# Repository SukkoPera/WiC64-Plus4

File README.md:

# WiC64-Plus4

WiC64-Plus4 is a WiFi network interface compatible with the Commodore 64, Commodore 16, 116 and Plus/4 computers.

## Summary
This is a slightly modified version of the [WiC64](https://github.com/WiC64-Team/wic64-hardware) board by GMP.

The most significant change is that the board can now be powered with either +5VDC or 9VAC.

This was done in order to make it easier to use the board on the Commodore 16 and Plus/4, where it must be connected through [an intermediate board](https://github.com/SukkoPera/PlusVIA) which only provides +5VDC.

Selection of the power source is automatic. If both power sources are available the higher one will take precedence. This means that **the board retains full compatibility with the C64**, and it will still use the 9VAC supply when connected to it.

Since the board might have a quite impulsive power draw, a ferrite bead was added on the +5VDC rail in order to reduce any interference.

Finally, to make hand-assembly easier, the 0603 components were switch to 0805 and the pads for the SOT-23 MOSFETs where made longer.

## Usage and Programming
This version of the board is **100% compatible with the original** one.

Please refer to [the original project](https://github.com/WiC64-Team/wic64-hardware) for assembly instructions, BOM (note you will need an extra 1n5819 diode) and 3D-printable enclosures.

The board is supposed to be used with [the original firmware](https://github.com/WiC64-Team/wic64-firmware).

For software support, I have made [a modified version of the interface library](https://github.com/SukkoPera/wic64-library) that allows writing software for either the C64 or C16/Plus4, but the board also works with the original library when used on the C64.

## Releases
If you want to get this board produced, you are recommended to get [the latest release](https://github.com/SukkoPera/WiC64-Plus4/releases) rather than the current git version, as the latter might be under development and is not guaranteed to be working.

Every release is accompanied by its Bill Of Materials (BOM) file and any relevant notes about it, which you are recommended to read carefully.

## License
The WiC64-Plus4 documentation, including the design itself, is copyright &copy; 2021 GMP and SukkoPera 2024-2026 and is licensed under the [Creative Commons Attribution 4.0 International License](https://creativecommons.org/licenses/by/4.0/).

This documentation is distributed *as is* and WITHOUT ANY EXPRESS OR IMPLIED WARRANTIES whatsoever with respect to its functionality, operability or use, including, without limitation, any implied warranties OF MERCHANTABILITY, SATISFACTORY QUALITY, FITNESS FOR A PARTICULAR PURPOSE or infringement. We expressly disclaim any liability whatsoever for any direct, indirect, consequential, incidental or special damages, including, without limitation, lost revenues, lost profits, losses resulting from business interruption or loss of data, regardless of the form of action or legal theory under which the liability may be asserted, even if advised of the possibility or likelihood of such damages.

## Support the Project
If you want to get some boards manufactured, you can get them from PCBWay through this link:

You get my gratitude and cheap, professionally-made and good quality PCBs, I get some credit that will help with this and [other projects](https://www.pcbway.com/project/member/shareproject/?bmbid=41100). You won't even have to worry about the various PCB options, it's all pre-configured for you!

Also, if you still have to register, [you can use this link](https://www.pcbway.com/setinvite.aspx?inviteid=41100) to get some bonus initial credit (and earn me some more).

You can also buy me a coffee if you want.

## Thanks
* GMP and the WiC64 team for the original board, library and whole concept.

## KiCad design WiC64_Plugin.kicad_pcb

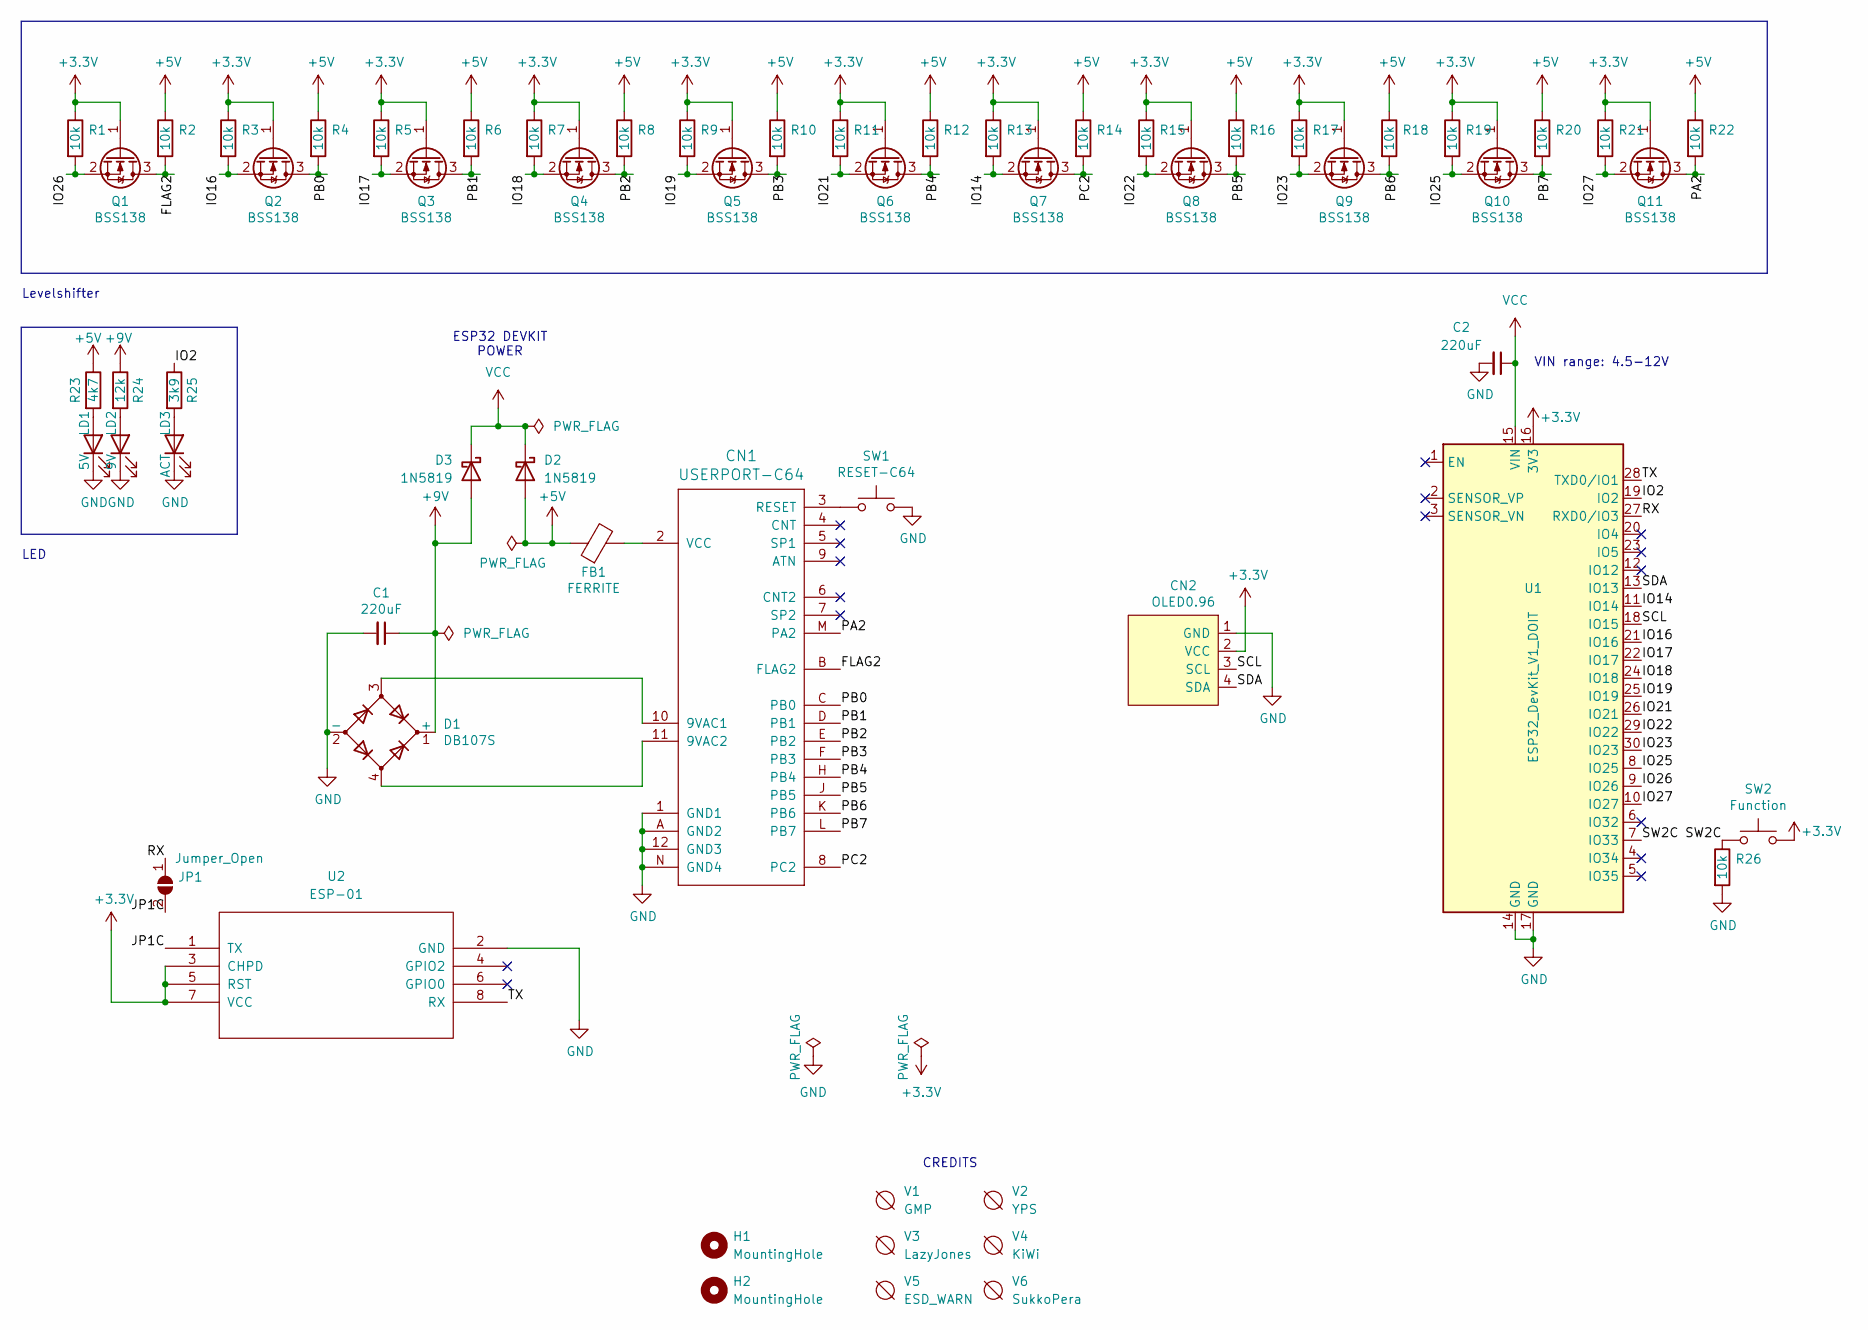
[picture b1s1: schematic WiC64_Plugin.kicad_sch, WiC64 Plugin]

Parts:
C1: 220uF; CP_6.3x11mm_horiz-R; LCSC C269997
C2: 220uF; CP_6.3x11mm_horiz-R; LCSC C106598
CN1: USERPORT-C64; UPS24CONN
CN2: OLED0.96; PinSocket_1x04_P2.54mm_Vertical
D1: DB107S; Diode_Bridge_Diotec_SO-DIL-Slim; LCSC C190797
D2, D3: 1N5819; D_SMA; LCSC C402219
FB1: FERRITE; Ferrite_D6.0mm_L10.00mm_Horizontal
H1, H2: MountingHole; MountingHole_3.2mm_M3_ISO7380
JP1: Jumper_Open; SolderJumper-2_P1.3mm_Open_RoundedPad1.0x1.5mm
LD1: 5V; LED_D3.0mm; LCSC C568936
LD2: 9V; LED_D3.0mm; LCSC C568937
LD3: ACT; LED_D3.0mm; LCSC C331056
Q1, Q2, Q3, Q4, Q5, Q6, Q7, Q8, Q9, Q10, Q11: BSS138; SOT-23; LCSC C112239
R1, R2, R3, R4, R5, R6, R7, R8, R9, R10, R11, R12, R13, R14, R15, R16, R17, R18, R19, R20, R21, R22, R26: 10k; R_0805_2012Metric_Pad1.20x1.40mm_HandSolder; LCSC C25804
R23: 4k7; R_0805_2012Metric_Pad1.20x1.40mm_HandSolder; LCSC C23162
R24: 12k; R_0805_2012Metric_Pad1.20x1.40mm_HandSolder; LCSC C22790
R25: 3k9; R_0805_2012Metric_Pad1.20x1.40mm_HandSolder; LCSC C23018
SW1: RESET-C64; SW_Tactile_SPST_Angled_PTS645Vx58-2LFS; LCSC C406160
SW2: Function; SW_Tactile_SPST_Angled_PTS645Vx58-2LFS; LCSC C406160
U1: ESP32_DevKit_V1_DOIT; esp32_devkit_v1_doit
U2: ESP-01
V1: GMP
V2: YPS; YPS2
V3: LazyJones; LazyJones2
V4: KiWi
V5: ESD_WARN; ESD-Logo_6.6x6mm_SilkScreen
V6: SukkoPera; PearLogo

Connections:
+3.3V: CN2.2 (VCC), Q1.1 (G), Q2.1 (G), Q3.1 (G), Q4.1 (G), Q5.1 (G), Q6.1 (G), Q7.1 (G), Q8.1 (G), Q9.1 (G), Q10.1 (G), Q11.1 (G), R1.1, R3.1, R5.1, R7.1, R9.1, R11.1, R13.1, R15.1, R17.1, R19.1, R21.1, SW2.2, U1.16 (3V3), U2.3 (CHPD), U2.5 (RST), U2.7 (VCC)
+5V: D2.2 (A), FB1.1, R2.1, R4.1, R6.1, R8.1, R10.1, R12.1, R14.1, R16.1, R18.1, R20.1, R22.1, R23.1
+9V: C1.1, D1.1 (+), D3.2 (A), R24.1
/FLAG2: CN1.B (FLAG2), Q1.3 (D), R2.2
/IO2: R25.1, U1.19 (IO2)
/IO14: Q7.2 (S), R13.2, U1.11 (IO14)
/IO16: Q2.2 (S), R3.2, U1.21 (IO16)
/IO17: Q3.2 (S), R5.2, U1.22 (IO17)
/IO18: Q4.2 (S), R7.2, U1.24 (IO18)
/IO19: Q5.2 (S), R9.2, U1.25 (IO19)
/IO21: Q6.2 (S), R11.2, U1.26 (IO21)
/IO22: Q8.2 (S), R15.2, U1.29 (IO22)
/IO23: Q9.2 (S), R17.2, U1.30 (IO23)
/IO25: Q10.2 (S), R19.2, U1.8 (IO25)
/IO26: Q1.2 (S), R1.2, U1.9 (IO26)
/IO27: Q11.2 (S), R21.2, U1.10 (IO27)
/JP1C: JP1.2 (B), U2.1 (TX)
/PA2: CN1.M (PA2), Q11.3 (D), R22.2
/PB0: CN1.C (PB0), Q2.3 (D), R4.2
/PB1: CN1.D (PB1), Q3.3 (D), R6.2
/PB2: CN1.E (PB2), Q4.3 (D), R8.2
/PB3: CN1.F (PB3), Q5.3 (D), R10.2
/PB4: CN1.H (PB4), Q6.3 (D), R12.2
/PB5: CN1.J (PB5), Q8.3 (D), R16.2
/PB6: CN1.K (PB6), Q9.3 (D), R18.2
/PB7: CN1.L (PB7), Q10.3 (D), R20.2
/PC2: CN1.8 (PC2), Q7.3 (D), R14.2
/RX: JP1.1 (A), U1.27 (RXD0/IO3)
/SCL: CN2.3 (SCL), U1.18 (IO15)
/SDA: CN2.4 (SDA), U1.13 (IO13)
/SW2C: R26.1, SW2.1, U1.7 (IO33)
/TX: U1.28 (TXD0/IO1), U2.8 (RX)
GND: C1.2, C2.2, CN1.1 (GND1), CN1.12 (GND3), CN1.A (GND2), CN1.N (GND4), CN2.1 (GND), D1.2 (-), LD1.1 (K), LD2.1 (K), LD3.1 (K), R26.2, SW1.2, U1.14 (GND), U1.17 (GND), U2.2 (GND)
unnamed: CN1.10 (9VAC1), D1.3
unnamed: CN1.11 (9VAC2), D1.4
unnamed: CN1.3 (RESET), SW1.1
unnamed: CN1.2 (VCC), FB1.2
unnamed: LD1.2 (A), R23.2
unnamed: LD2.2 (A), R24.2
unnamed: LD3.2 (A), R25.2
VCC: C2.1, D2.1 (K), D3.1 (K), U1.15 (VIN)

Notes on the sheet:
VIN range: 4.5-12V
CREDITS
Levelshifter
LED
ESP32 DEVKIT POWER

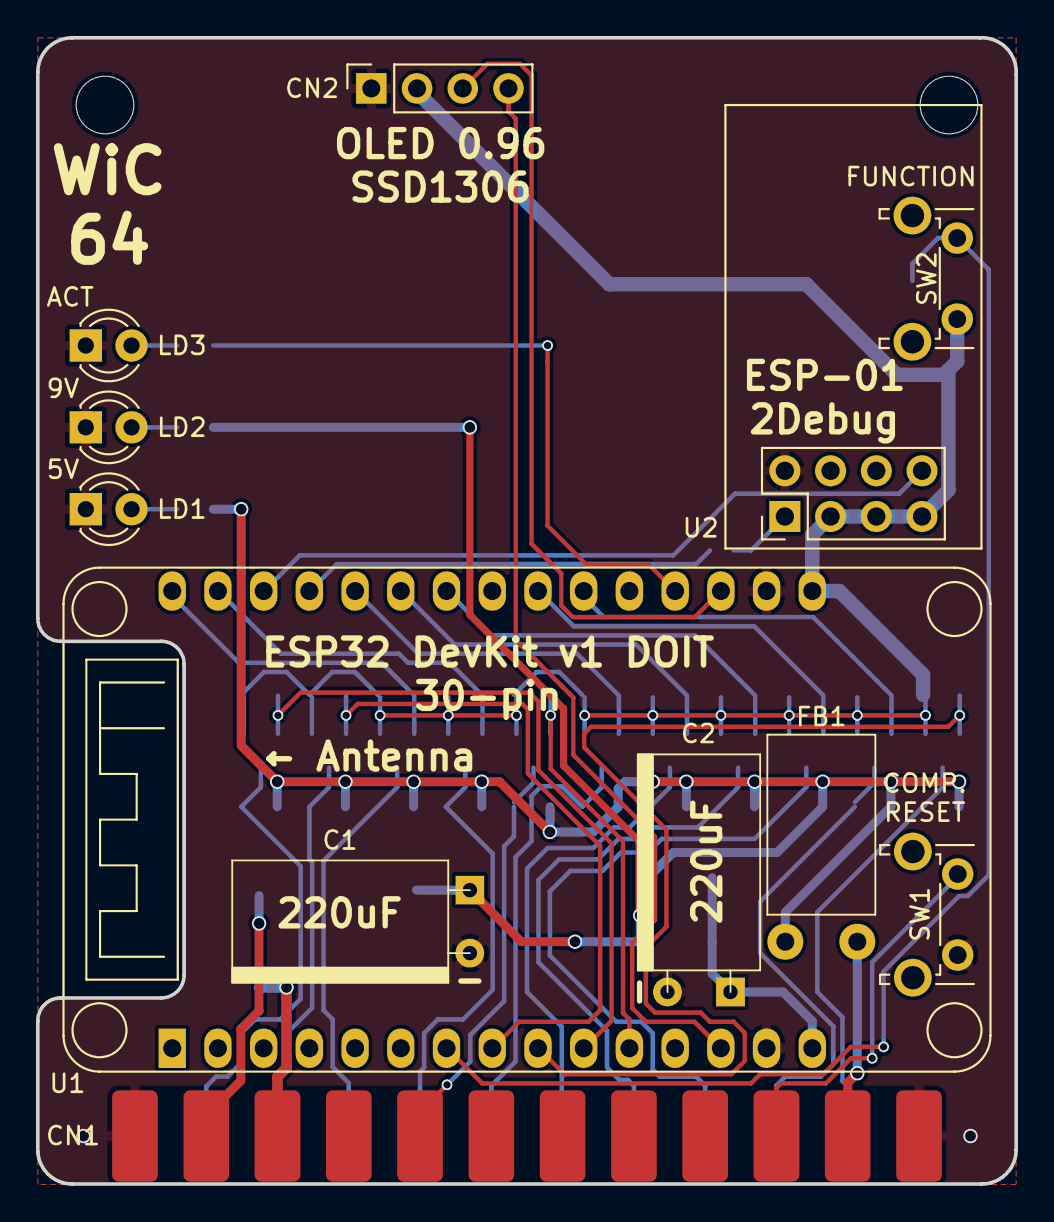
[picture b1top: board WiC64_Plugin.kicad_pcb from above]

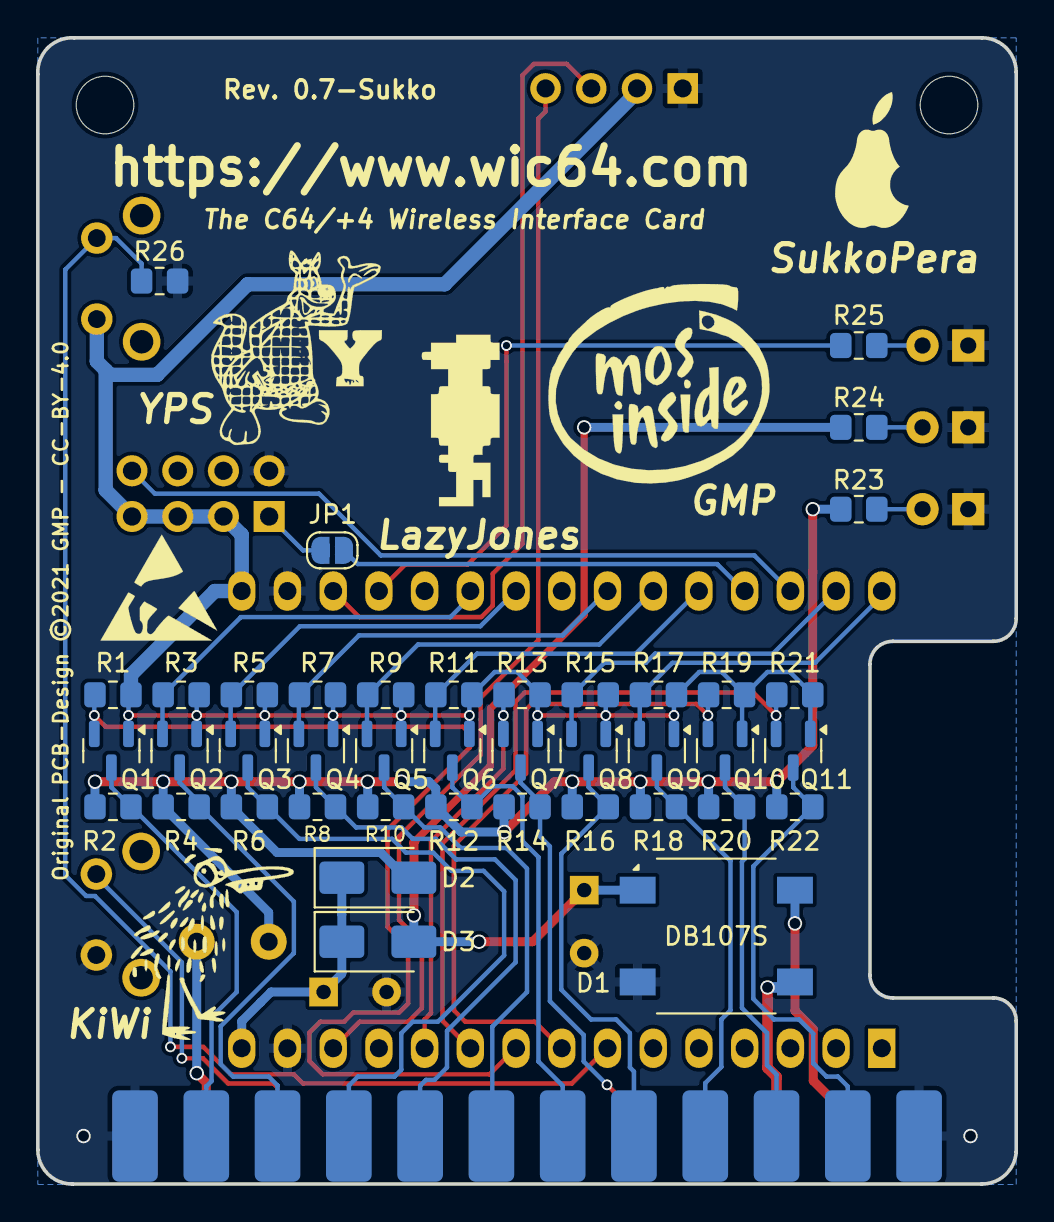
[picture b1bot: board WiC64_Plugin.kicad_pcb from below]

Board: 2 copper layers, 54.4 x 63.7 mm, 61 parts (47 on the bottom side), 41 nets.

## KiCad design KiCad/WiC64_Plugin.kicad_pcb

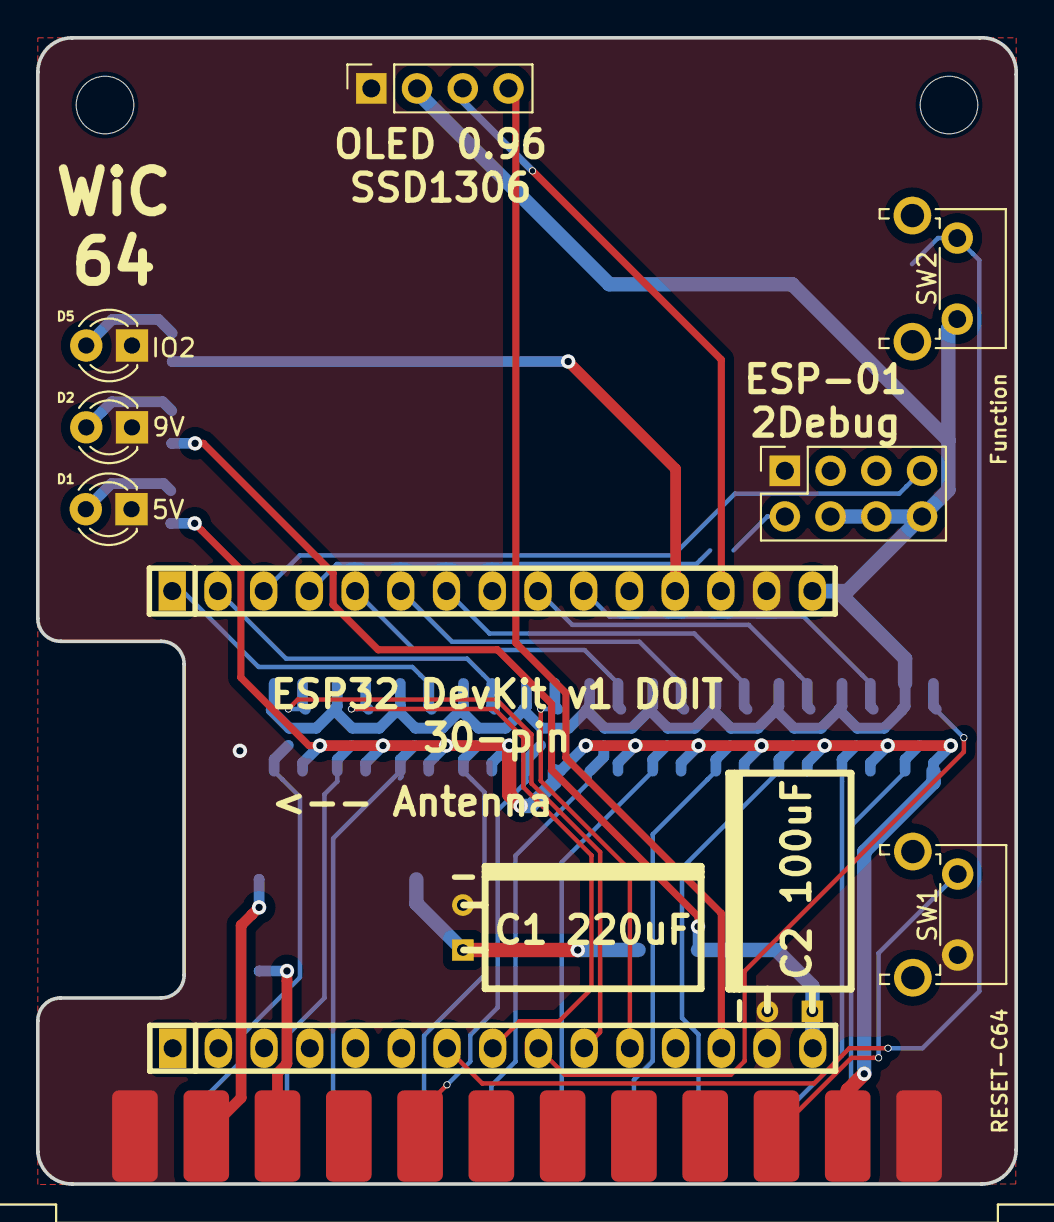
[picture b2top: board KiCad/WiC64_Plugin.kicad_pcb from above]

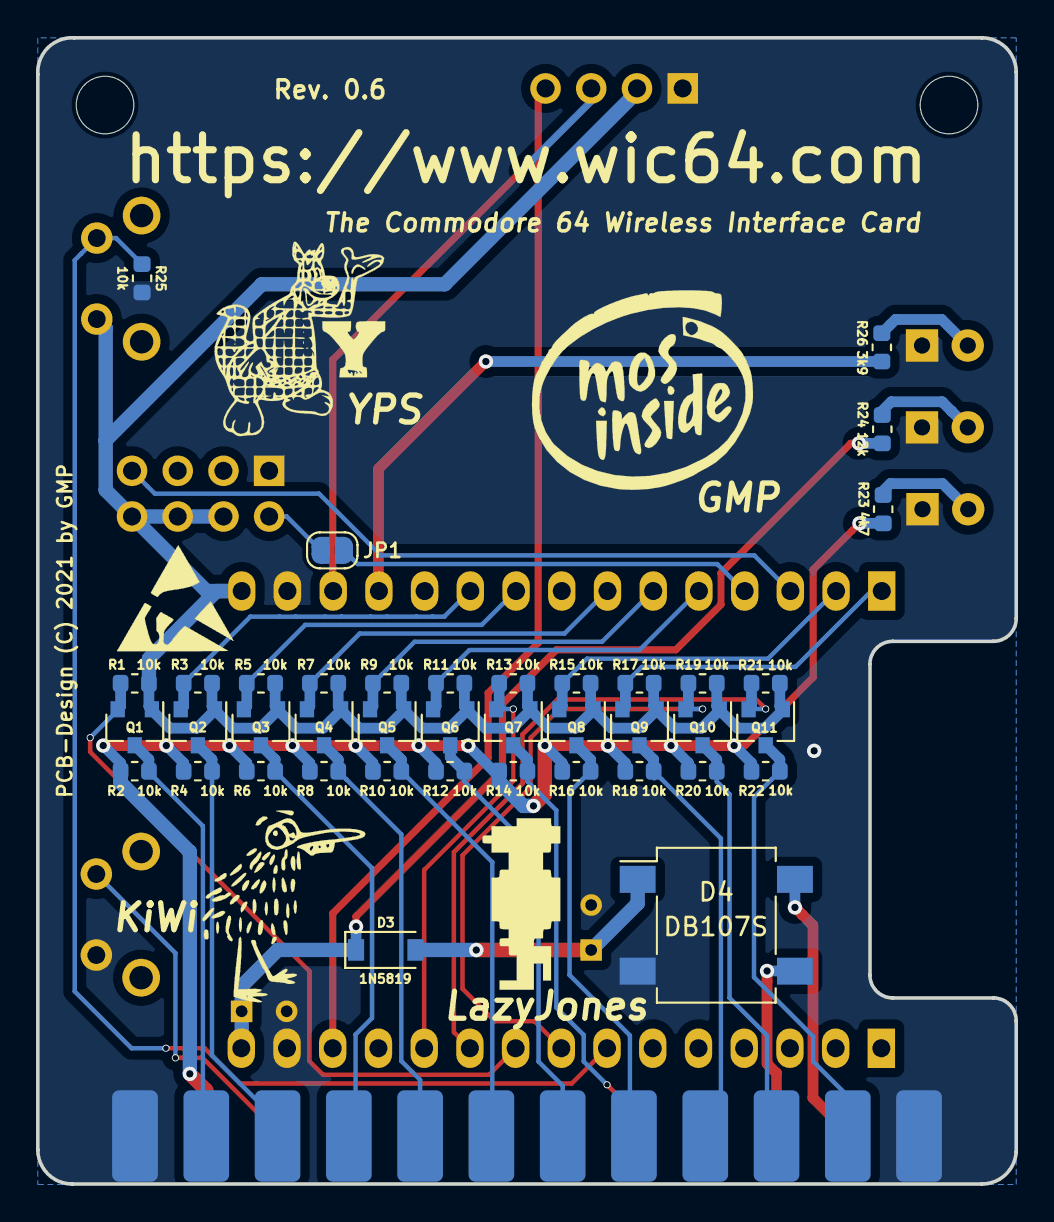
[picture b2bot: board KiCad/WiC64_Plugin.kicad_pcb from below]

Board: 2 copper layers, 54.4 x 63.7 mm, 52 parts (40 on the bottom side), 40 nets.

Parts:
C1: 220uF; CP_6.3x11mm_hor
C2: 100uF; CP_6.3x11mm_hor
CN1: USERPORT-C64; UPS24CONN
D1: 5V; LED_D3.0mm
D2: 9V; LED_D3.0mm
D3: 1N5819; D_SOD-123
D4: DB107S; Diode_Bridge_Diotec_SO-DIL-Slim
D5: IO2; LED_D3.0mm
JP1: Jumper_Open; SolderJumper-2_P1.3mm_Open_RoundedPad1.0x1.5mm
Q1, Q2, Q3, Q4, Q5, Q6, Q7, Q8, Q9, Q10, Q11: BSS138; SOT-23
R1, R2, R3, R4, R5, R6, R7, R8, R9, R10, R11, R12, R13, R14, R15, R16, R17, R18, R19, R20, R21, R22, R25: 10k; R_0603_1608Metric
R23: 4k7; R_0603_1608Metric
R24: 12k; R_0603_1608Metric
R26: 3k9; R_0603_1608Metric
SW1: RESET-C64; SW_Tactile_SPST_Angled_PTS645Vx58-2LFS
SW2: Function; SW_Tactile_SPST_Angled_PTS645Vx58-2LFS
XBrd1: Conn_01x04_Female; PinSocket_1x04_P2.54mm_Vertical
XU1-1, XU1-2: Conn_01x15_Female; pin_socket_15
XU2: HEADER_4x2; PinSocket_2x04_P2.54mm_Vertical

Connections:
+3.3V: Q1.1 (G), Q2.1 (G), Q3.1 (G), Q4.1 (G), Q5.1 (G), Q6.1 (G), Q7.1 (G), Q8.1 (G), Q9.1 (G), Q10.1 (G), Q11.1 (G), R1.1, R3.1, R5.1, R7.1, R9.1, R11.1, R13.1, R15.1, R17.1, R19.1, R21.1, SW2.2, XBrd1.2, XU1-2.15, XU2.4, XU2.6, XU2.8
+5V: CN1.2 (VCC), R2.1, R4.1, R6.1, R8.1, R10.1, R12.1, R14.1, R16.1, R18.1, R20.1, R22.1, R23.1
/FLAG2: CN1.B (FLAG2), Q1.3 (D), R2.2
/IO2: R26.1, XU1-2.12
/IO14: Q7.2 (S), R13.2, XU1-1.11
/IO16: Q2.2 (S), R3.2, XU1-2.10
/IO17: Q3.2 (S), R5.2, XU1-2.9
/IO18: Q4.2 (S), R7.2, XU1-2.7
/IO19: Q5.2 (S), R9.2, XU1-2.6
/IO21: Q6.2 (S), R11.2, XU1-2.5
/IO22: Q8.2 (S), R15.2, XU1-2.2
/IO23: Q9.2 (S), R17.2, XU1-2.1
/IO25: Q10.2 (S), R19.2, XU1-1.8
/IO26: Q1.2 (S), R1.2, XU1-1.9
/IO27: Q11.2 (S), R21.2, XU1-1.10
/JP1C: JP1.2 (B), XU2.2
/PA2: CN1.M (PA2), Q11.3 (D), R22.2
/PB0: CN1.C (PB0), Q2.3 (D), R4.2
/PB1: CN1.D (PB1), Q3.3 (D), R6.2
/PB2: CN1.E (PB2), Q4.3 (D), R8.2
/PB3: CN1.F (PB3), Q5.3 (D), R10.2
/PB4: CN1.H (PB4), Q6.3 (D), R12.2
/PB5: CN1.J (PB5), Q8.3 (D), R16.2
/PB6: CN1.K (PB6), Q9.3 (D), R18.2
/PB7: CN1.L (PB7), Q10.3 (D), R20.2
/PC2: CN1.8 (PC2), Q7.3 (D), R14.2
/RX: JP1.1 (A), XU1-2.4
/SCL: XBrd1.3, XU1-2.13
/SDA: XBrd1.4, XU1-1.13
/SW2C: R25.1, SW2.1, XU1-1.7
/TX: XU1-2.3, XU2.7
/VIN: C2.1, D3.1 (K), R24.1, XU1-1.15
GND: C1.2, C2.2, CN1.1 (GND1), CN1.12 (GND3), CN1.A (GND2), CN1.N (GND4), D1.1 (K), D2.1 (K), D4.2 (-), D5.1 (K), R25.2, SW1.2, XBrd1.1, XU1-1.14, XU1-2.14, XU2.1
unnamed: CN1.10 (9VAC1), D4.3
unnamed: CN1.11 (9VAC2), D4.4
unnamed: CN1.3 (RESET), SW1.1
unnamed: D1.2 (A), R23.2
unnamed: D2.2 (A), R24.2
unnamed: C1.1, D3.2 (A), D4.1 (+)
unnamed: D5.2 (A), R26.2

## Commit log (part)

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2024-05-24 Fix board outline (and port to KiCad 8)
2024-05-24 Find/Reconstruct missing libs/footprints and fix most DRC problems PCB is mostly untouched so far, focus was just on "completing" the released source files
2024-05-25 Add .gitignore
2024-05-25 Move all files to root directory
2024-05-25 Make all resistors 0805
2024-05-25 Add 3D models
2024-05-26 Remove redundant symbols
2024-05-26 Allow powering ESP32 from 5V
2024-05-26 Update gerber path
2024-05-26 Move all footprints to single library
2024-05-28 Initial +4 version
2024-06-02 Complete changes for +4 version
2024-06-07 Add renders
2024-06-14 Final touches for C64 version
2024-06-14 Move SCL/SDA tracks around
2024-06-23 Latch FLAG2
2024-06-23 Final touches for V1FF
2024-09-09 Add Schmitt trigger to clean TX signal
2025-01-21 Various refinements for V1FFF
2025-01-21 Final-final-final touches
2025-11-24 Add diode so that power source is selected automatically
2025-11-24 Add Pear logo + Connect 9V power led to actual 9V
2026-02-05 Fix ERC

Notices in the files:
KiCad/WiC64_Plugin.kicad_pcb:
(C) 2021 by GMP
PCB-Design (C) 2021 by GMP
WiC64_Plugin.kicad_pcb:
Original PCB-Design ©2021 GMP - CC-BY-4.0
